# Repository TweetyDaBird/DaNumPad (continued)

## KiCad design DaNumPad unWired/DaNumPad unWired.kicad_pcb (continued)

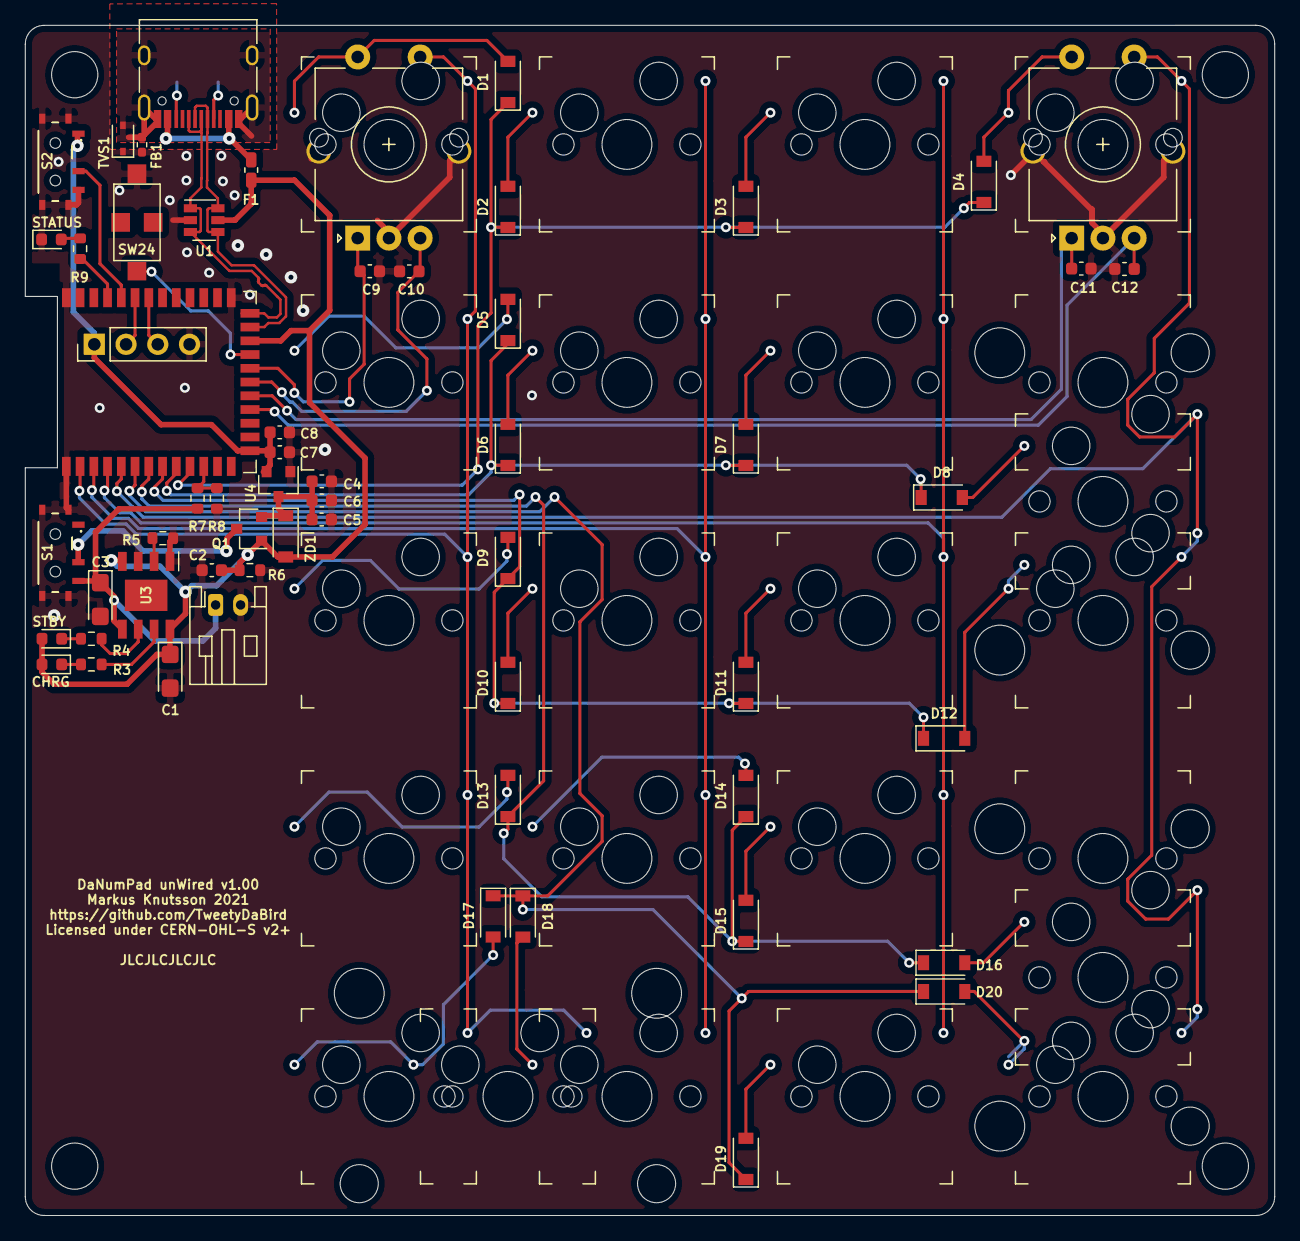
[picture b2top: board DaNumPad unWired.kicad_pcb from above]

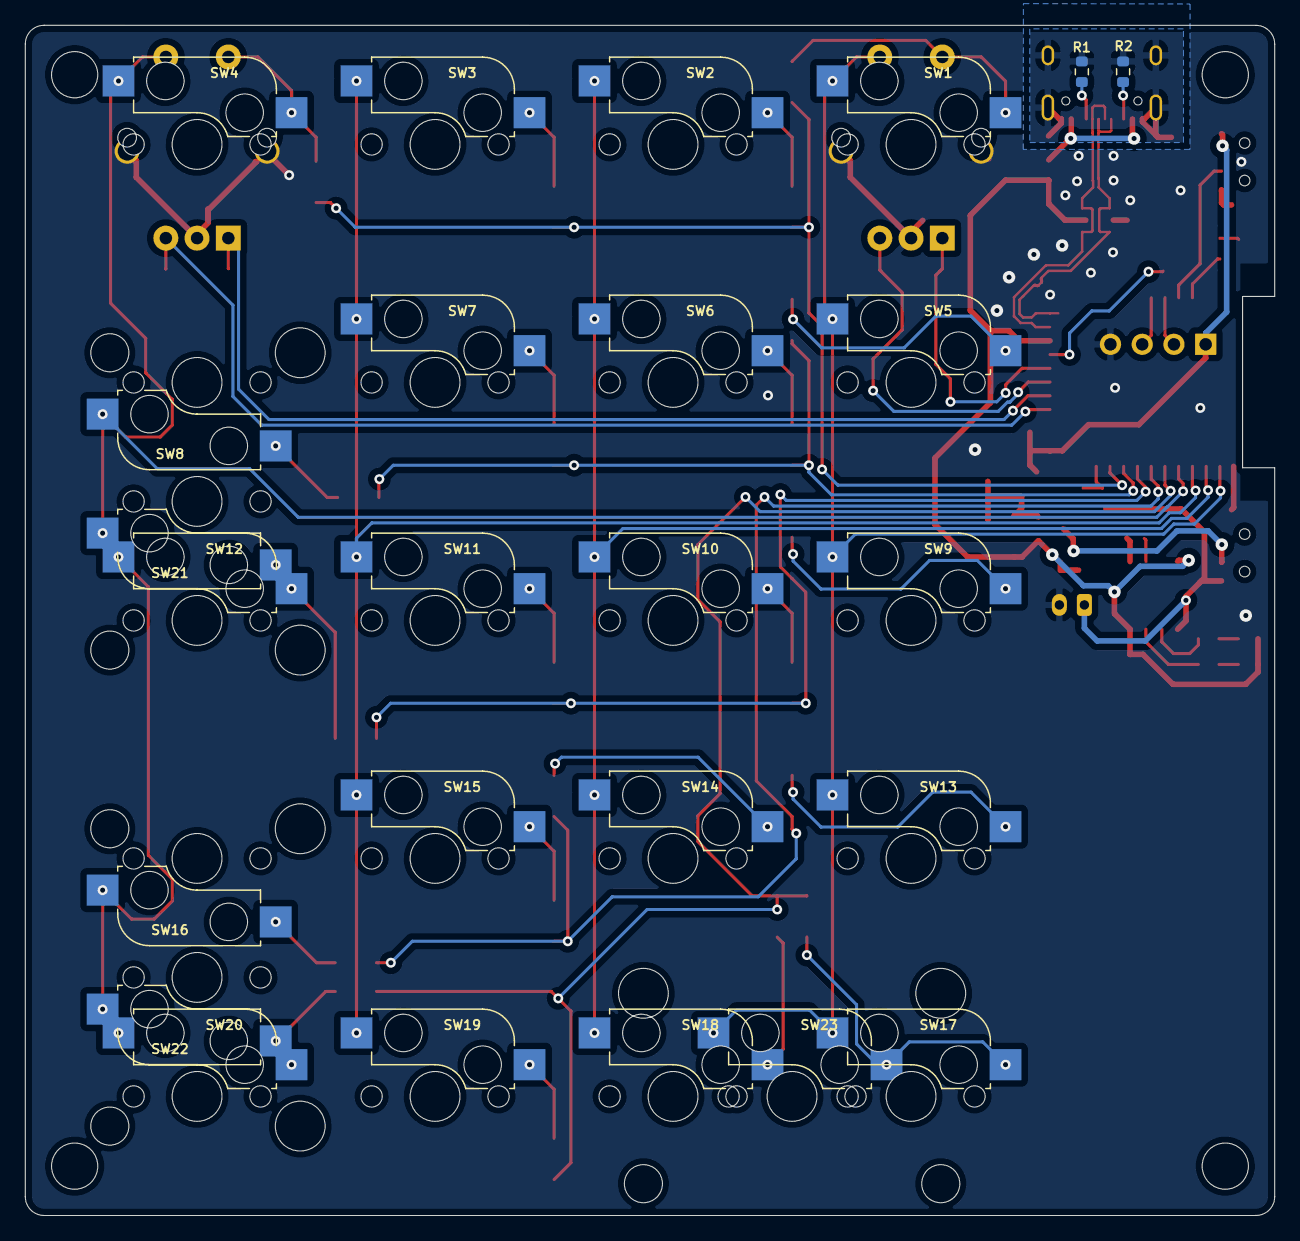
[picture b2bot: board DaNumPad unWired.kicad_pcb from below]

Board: 2 copper layers, 100.0 x 95.3 mm, 91 parts (2 on the bottom side), 57 nets.

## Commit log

2021-08-25 Added license
2021-08-25 Added silkscreen and PCB Plates
2021-08-25 Updated plates
2021-08-25 Deleted old files
2021-08-30 Glow version redesign
    For now, it's 17 keys only.
2021-08-31 Finalized licensing on PCB files
2021-08-31 Cleanup of silkscreen
2021-09-09 Added Glow 20 key version
